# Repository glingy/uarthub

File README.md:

# UART Hub

This is a 6-port "null modem cable". There are six 4-signal UART channels with flow control. Each channel is connected to all six RP2040's at each USB port to allow full software configuration of which USB ports communicate on which channels. 

For example with the following configuration:
```
Channel 0: Port 0, Port 1
Channel 1: Port 0, Port 2
Channel 2: Port 1, Port 3
Channel 3: Port 1, Port 2
Channel 4: Port 0, Port 1
Channel 5: Port 0, External
```

A computer connected to USB 0 will see four USB CDC-ACM serial ports (COM ports on Windows, TTY's on Linux). They will be connected to USB 1, USB 2, USB 1, and the external pins labeled `5` respectively. Port 1 will also have four serial ports (USB 0, USB 3, USB 2, USB 0). Note that in this case there are two independent serial connections between USB 0 and 1. USB 2 will have two serial ports, USB 3 will only see one port, and USB 4 & 5 will see no serial ports. 

USB 0 will also have an additional management serial port that allows runtime configuration of which ports are associated with each channel via a terminal-based UI.

This project is not intended to work for other protocols (I2C, SPI), but the hardware should be capable of supporting I2C or SPI devices on the external pins, the RP2040 uses the same pins for I2C/SPI as it does for UART.

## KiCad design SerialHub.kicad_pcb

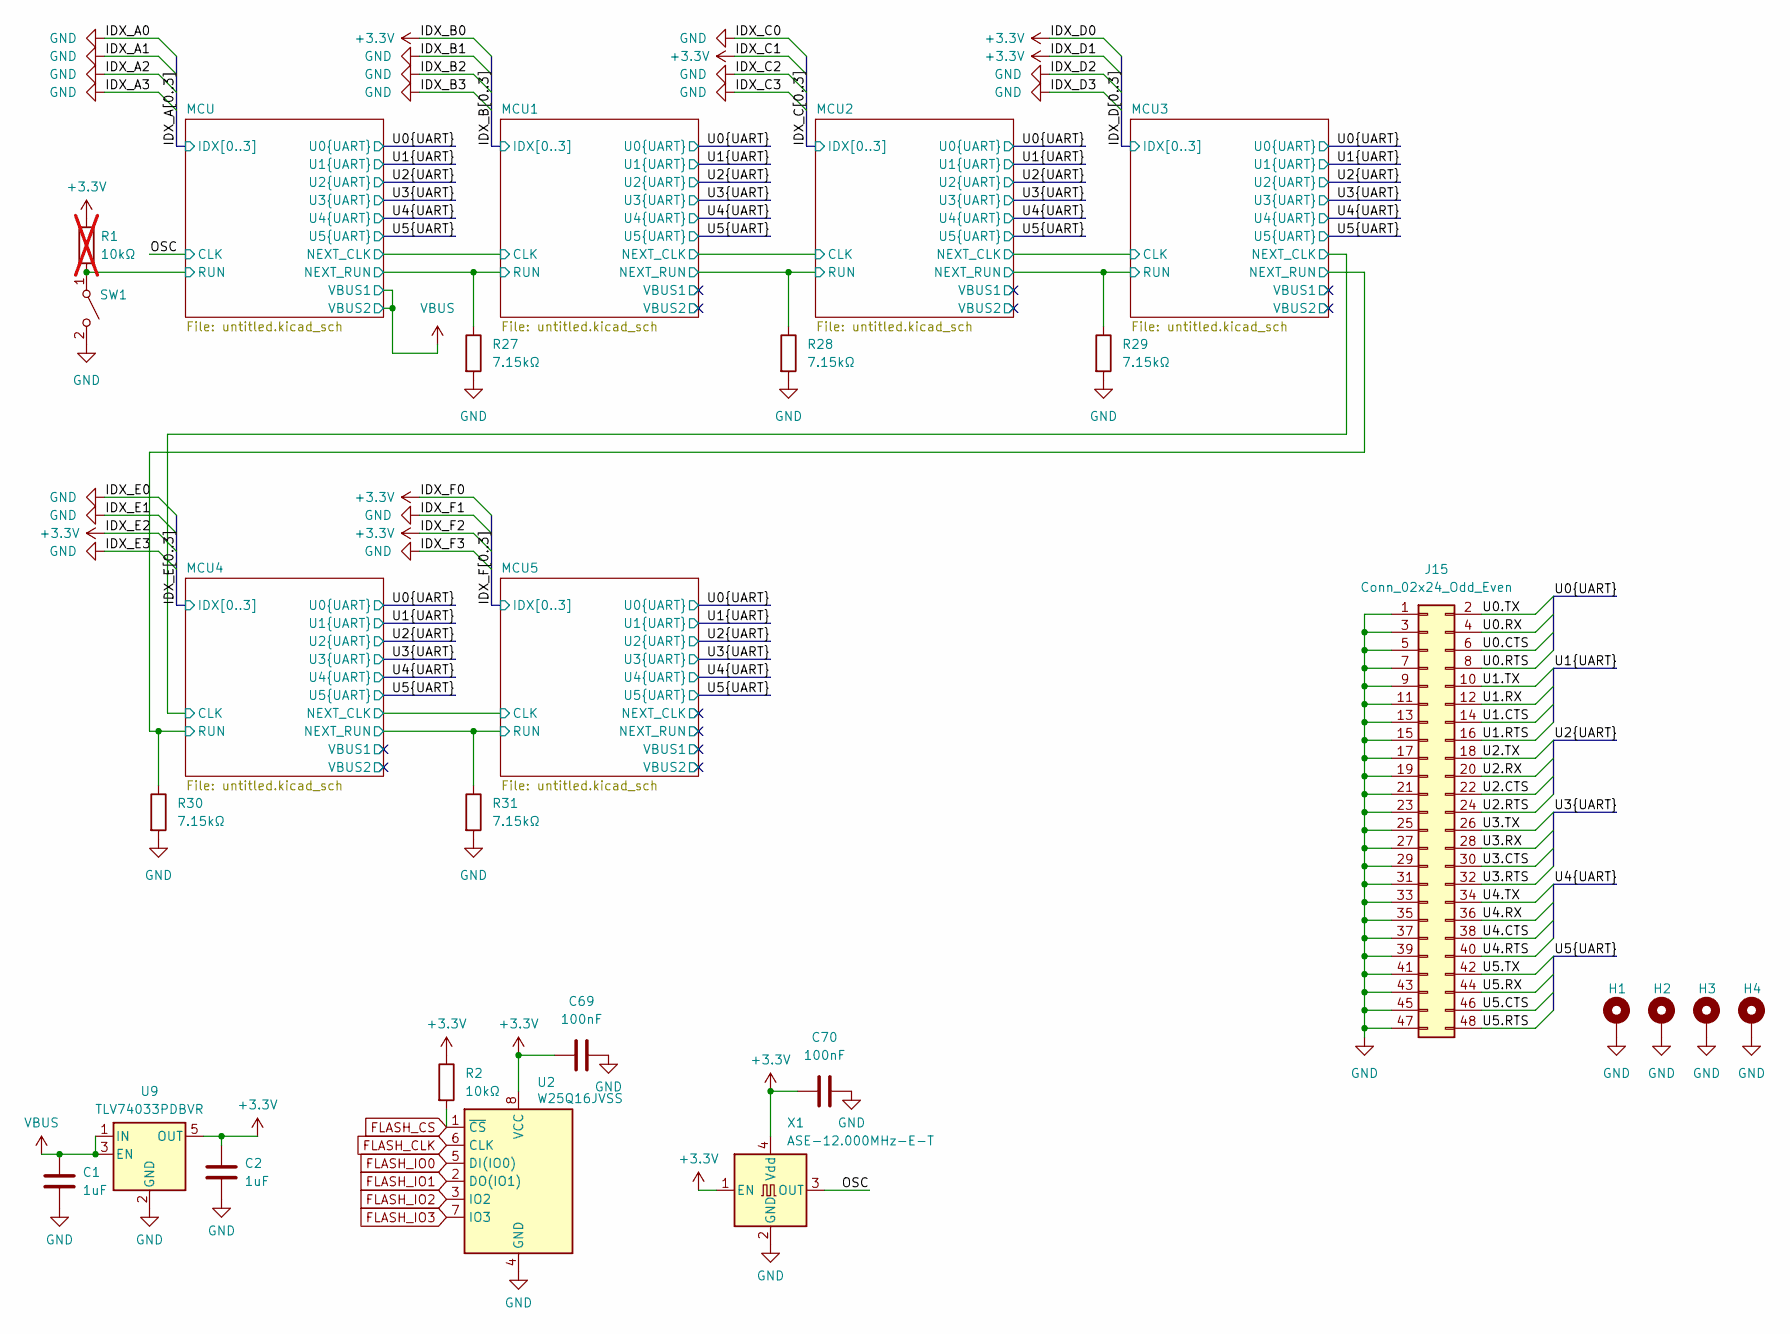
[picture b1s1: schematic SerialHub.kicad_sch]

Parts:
C1, C2: 1uF; C_0402_1005Metric; Digikey 399-C0402C105K9PACTUCT-ND
C69, C70: 100nF; C_0402_1005Metric; Digikey 399-C0402C105K9PACTUCT-ND
H1, H2, H3, H4: MountingHole_Pad; MountingHole_3.2mm_M3_Pad
J15: Conn_02x24_Odd_Even; PinHeader_2x24_P2.54mm_Vertical
R1: 10kΩ; R_0402_1005Metric; Digikey 311-10KJRCT-ND; not fitted
R2: 10kΩ; R_0402_1005Metric; Digikey 311-10KJRCT-ND
R27, R28, R29, R30, R31: 7.15kΩ; R_0402_1005Metric; Digikey YAG3235CT-ND
SW1: SW_SPST; SW_PUSH_6mm_H4.3mm; Digikey 2223-TS02-66-43-BK-160-LCR-D-ND
U2: W25Q16JVSS; SOIC-8_5.3x5.3mm_P1.27mm; Digikey 256-W25Q16JVSSIQTRCT-ND
U9: TLV74033PDBVR; SOT-23-5; Digikey 296-TLV74033PDBVRCT-ND
X1: ASE-12.000MHz-E-T; Oscillator_SMD_Abracon_ASE-4Pin_3.2x2.5mm; Digikey 535-ASE-12.000MHZ-E-TCT-ND

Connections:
+3.3V: C2.1, C69.1, C70.1, R1.2, R2.1, U2.8 (VCC), U9.5 (OUT), X1.1 (EN), X1.4 (Vdd); also elsewhere on the board
/MCU1/NEXT_RUN: R28.1; also elsewhere on the board
/MCU2/NEXT_RUN: R29.1; also elsewhere on the board
/MCU3/NEXT_RUN: R30.1; also elsewhere on the board
/MCU4/NEXT_RUN: R31.1; also elsewhere on the board
/MCU/NEXT_RUN: R27.1; also elsewhere on the board
/MCU/RUN: R1.1, SW1.1 (A); also elsewhere on the board
/OSC: X1.3 (OUT); also elsewhere on the board
/U0.CTS: J15.6; also elsewhere on the board
/U0.RTS: J15.8; also elsewhere on the board
/U0.RX: J15.4; also elsewhere on the board
/U0.TX: J15.2; also elsewhere on the board
/U1.CTS: J15.14; also elsewhere on the board
/U1.RTS: J15.16; also elsewhere on the board
/U1.RX: J15.12; also elsewhere on the board
/U1.TX: J15.10; also elsewhere on the board
/U2.CTS: J15.22; also elsewhere on the board
/U2.RTS: J15.24; also elsewhere on the board
/U2.RX: J15.20; also elsewhere on the board
/U2.TX: J15.18; also elsewhere on the board
/U3.CTS: J15.30; also elsewhere on the board
/U3.RTS: J15.32; also elsewhere on the board
/U3.RX: J15.28; also elsewhere on the board
/U3.TX: J15.26; also elsewhere on the board
/U4.CTS: J15.38; also elsewhere on the board
/U4.RTS: J15.40; also elsewhere on the board
/U4.RX: J15.36; also elsewhere on the board
/U4.TX: J15.34; also elsewhere on the board
/U5.CTS: J15.46; also elsewhere on the board
/U5.RTS: J15.48; also elsewhere on the board
/U5.RX: J15.44; also elsewhere on the board
/U5.TX: J15.42; also elsewhere on the board
FLASH_CLK: U2.6 (CLK); also elsewhere on the board
FLASH_CS: R2.2, U2.1 (~CS); also elsewhere on the board
FLASH_IO0: U2.5 (DI(IO0)); also elsewhere on the board
FLASH_IO1: U2.2 (DO(IO1)); also elsewhere on the board
FLASH_IO2: U2.3 (IO2); also elsewhere on the board
FLASH_IO3: U2.7 (IO3); also elsewhere on the board
VBUS: C1.1, U9.1 (IN), U9.3 (EN); also elsewhere on the board

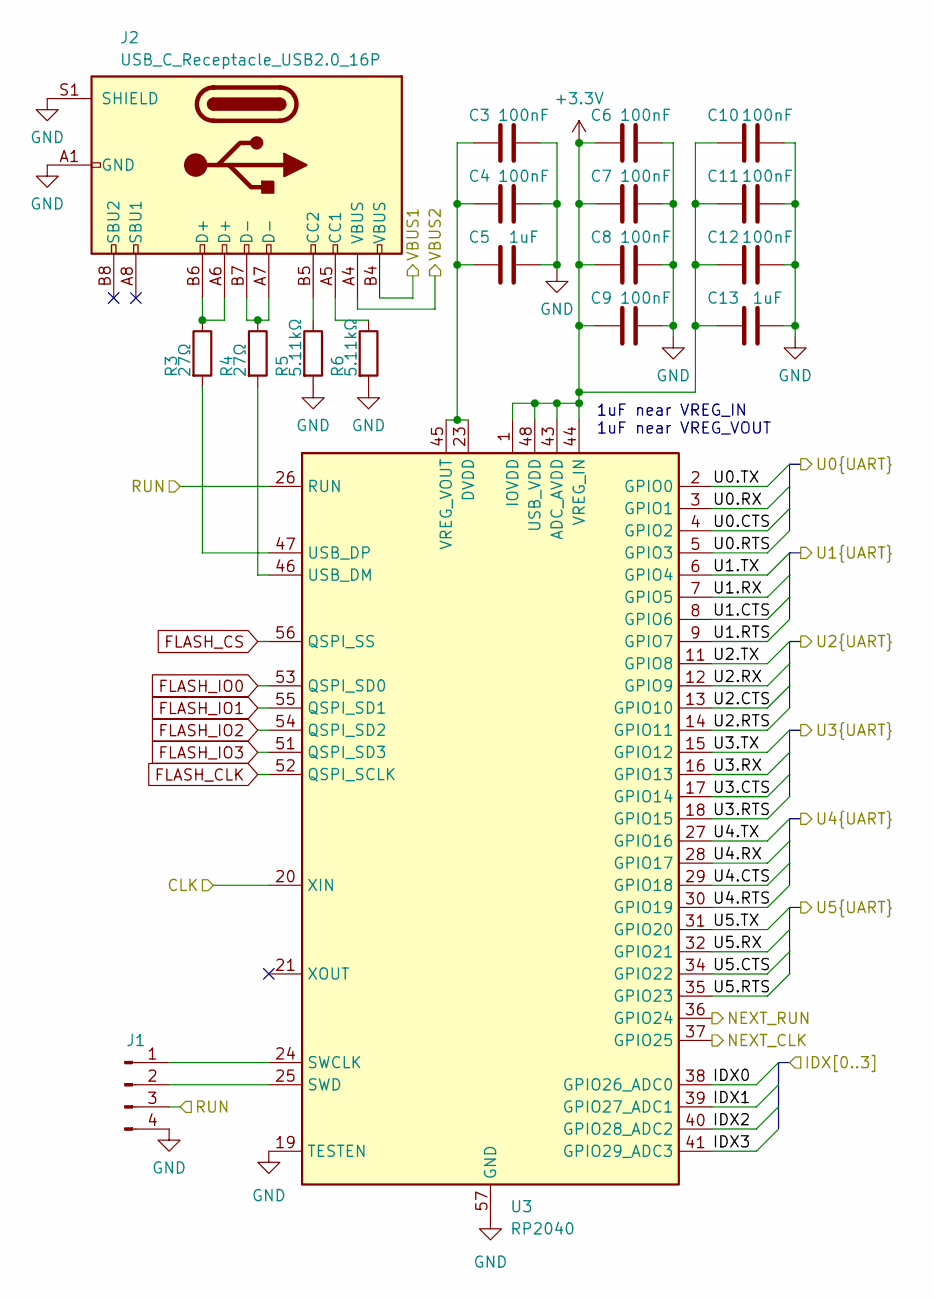
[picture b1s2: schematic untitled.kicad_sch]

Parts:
C3, C4, C6, C7, C8, C9, C10, C11, C12: 100nF; C_0402_1005Metric; Digikey 1276-1043-1-ND
C5, C13: 1uF; C_0402_1005Metric; Digikey 399-C0402C105K9PACTUCT-ND
J1: Conn_01x04_Pin; SaleaeTestpoint4
J2: USB_C_Receptacle_USB2.0_16P; SAMESKY_UJ20-C-H-G-SMT-1-P16-TR; Digikey 2223-UJ20-C-H-G-SMT-1-P16-TRCT-ND
R3, R4: 27Ω; R_0402_1005Metric; Digikey YAG5278CT-ND
R5, R6: 5.11kΩ; R_0402_1005Metric; Digikey RMCF0402FT5K11CT-ND
U3: RP2040; QFN-56-1EP_7x7mm_P0.4mm_EP3.2x3.2mm; Digikey 2648-SC0914(13)CT-ND

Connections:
+3.3V: C6.1, C7.1, C8.1, C9.1, C10.1, C11.1, C12.1, C13.1, U3.1 (IOVDD), U3.10 (IOVDD), U3.22 (IOVDD), U3.33 (IOVDD), U3.42 (IOVDD), U3.43 (ADC_AVDD), U3.44 (VREG_IN), U3.48 (USB_VDD), U3.49 (IOVDD); also elsewhere on the board
/MCU/NEXT_CLK: U3.37 (GPIO25); also elsewhere on the board
/MCU/NEXT_RUN: U3.36 (GPIO24); also elsewhere on the board
/MCU/RUN: J1.3, U3.26 (RUN); also elsewhere on the board
/OSC: U3.20 (XIN); also elsewhere on the board
/U0.CTS: U3.4 (GPIO2); also elsewhere on the board
/U0.RTS: U3.5 (GPIO3); also elsewhere on the board
/U0.RX: U3.3 (GPIO1); also elsewhere on the board
/U0.TX: U3.2 (GPIO0); also elsewhere on the board
/U1.CTS: U3.8 (GPIO6); also elsewhere on the board
/U1.RTS: U3.9 (GPIO7); also elsewhere on the board
/U1.RX: U3.7 (GPIO5); also elsewhere on the board
/U1.TX: U3.6 (GPIO4); also elsewhere on the board
/U2.CTS: U3.13 (GPIO10); also elsewhere on the board
/U2.RTS: U3.14 (GPIO11); also elsewhere on the board
/U2.RX: U3.12 (GPIO9); also elsewhere on the board
/U2.TX: U3.11 (GPIO8); also elsewhere on the board
/U3.CTS: U3.17 (GPIO14); also elsewhere on the board
/U3.RTS: U3.18 (GPIO15); also elsewhere on the board
/U3.RX: U3.16 (GPIO13); also elsewhere on the board
/U3.TX: U3.15 (GPIO12); also elsewhere on the board
/U4.CTS: U3.29 (GPIO18); also elsewhere on the board
/U4.RTS: U3.30 (GPIO19); also elsewhere on the board
/U4.RX: U3.28 (GPIO17); also elsewhere on the board
/U4.TX: U3.27 (GPIO16); also elsewhere on the board
/U5.CTS: U3.34 (GPIO22); also elsewhere on the board
/U5.RTS: U3.35 (GPIO23); also elsewhere on the board
/U5.RX: U3.32 (GPIO21); also elsewhere on the board
/U5.TX: U3.31 (GPIO20); also elsewhere on the board
FLASH_CLK: U3.52 (QSPI_SCLK); also elsewhere on the board
FLASH_CS: U3.56 (QSPI_SS); also elsewhere on the board
FLASH_IO0: U3.53 (QSPI_SD0); also elsewhere on the board
FLASH_IO1: U3.55 (QSPI_SD1); also elsewhere on the board
FLASH_IO2: U3.54 (QSPI_SD2); also elsewhere on the board
FLASH_IO3: U3.51 (QSPI_SD3); also elsewhere on the board
unnamed: J1.1, U3.24 (SWCLK)
unnamed: J1.2, U3.25 (SWD)
unnamed: J2.A5 (CC1), R6.1
unnamed: J2.B5 (CC2), R5.1
unnamed: J2.A6 (D+), J2.B6 (D+), R3.1
unnamed: J2.A7 (D-), J2.B7 (D-), R4.1
unnamed: R4.2, U3.46 (USB_DM)
unnamed: R3.2, U3.47 (USB_DP)
unnamed: C3.1, C4.1, C5.1, U3.23 (DVDD), U3.45 (VREG_VOUT), U3.50 (DVDD)
VBUS: J2.A4 (VBUS), J2.B4 (VBUS); also elsewhere on the board

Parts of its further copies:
C14, C15, C17, C18, C19, C20, C21, C22, C23, C25, C26, C28, C29, C30, C31, C32, C33, C34, C36, C37, C39, C40, C41, C42, C43, C44, C45, C47, C48, C50, C51, C52, C53, C54, C55, C56, C58, C59, C61, C62, C63, C64, C65, C66, C67: 100nF; C_0402_1005Metric; Digikey 1276-1043-1-ND
C16, C24, C27, C35, C38, C46, C49, C57, C60, C68: 1uF; C_0402_1005Metric; Digikey 399-C0402C105K9PACTUCT-ND
J3, J5, J7, J9, J11: Conn_01x04_Pin; SaleaeTestpoint4
J4, J6, J8, J10, J12: USB_C_Receptacle_USB2.0_16P; SAMESKY_UJ20-C-H-G-SMT-1-P16-TR; Digikey 2223-UJ20-C-H-G-SMT-1-P16-TRCT-ND
R7, R8, R11, R12, R15, R16, R19, R20, R23, R24: 27Ω; R_0402_1005Metric; Digikey YAG5278CT-ND
R9, R10, R13, R14, R17, R18, R21, R22, R25, R26: 5.11kΩ; R_0402_1005Metric; Digikey RMCF0402FT5K11CT-ND
U4, U5, U6, U7, U8: RP2040; QFN-56-1EP_7x7mm_P0.4mm_EP3.2x3.2mm; Digikey 2648-SC0914(13)CT-ND

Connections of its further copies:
+3.3V: C17.1, C18.1, C19.1, C20.1, C21.1, C22.1, C23.1, C24.1, C28.1, C29.1, C30.1, C31.1, C32.1, C33.1, C34.1, C35.1, C39.1, C40.1, C41.1, C42.1, C43.1, C44.1, C45.1, C46.1, C50.1, C51.1, C52.1, C53.1, C54.1, C55.1, C56.1, C57.1, C61.1, C62.1, C63.1, C64.1, C65.1, C66.1, C67.1, C68.1, U4.1 (IOVDD), U4.10 (IOVDD), U4.22 (IOVDD), U4.33 (IOVDD), U4.38 (GPIO26_ADC0), U4.42 (IOVDD), U4.43 (ADC_AVDD), U4.44 (VREG_IN), U4.48 (USB_VDD), U4.49 (IOVDD), U5.1 (IOVDD), U5.10 (IOVDD), U5.22 (IOVDD), U5.33 (IOVDD), U5.39 (GPIO27_ADC1), U5.42 (IOVDD), U5.43 (ADC_AVDD), U5.44 (VREG_IN), U5.48 (USB_VDD), U5.49 (IOVDD), U6.1 (IOVDD), U6.10 (IOVDD), U6.22 (IOVDD), U6.33 (IOVDD), U6.38 (GPIO26_ADC0), U6.39 (GPIO27_ADC1), U6.42 (IOVDD), U6.43 (ADC_AVDD), U6.44 (VREG_IN), U6.48 (USB_VDD), U6.49 (IOVDD), U7.1 (IOVDD), U7.10 (IOVDD), U7.22 (IOVDD), U7.33 (IOVDD), U7.40 (GPIO28_ADC2), U7.42 (IOVDD), U7.43 (ADC_AVDD), U7.44 (VREG_IN), U7.48 (USB_VDD), U7.49 (IOVDD), U8.1 (IOVDD), U8.10 (IOVDD), U8.22 (IOVDD), U8.33 (IOVDD), U8.38 (GPIO26_ADC0), U8.40 (GPIO28_ADC2), U8.42 (IOVDD), U8.43 (ADC_AVDD), U8.44 (VREG_IN), U8.48 (USB_VDD), U8.49 (IOVDD); also elsewhere on the board
/MCU1/NEXT_CLK: U4.37 (GPIO25), U5.20 (XIN)
/MCU1/NEXT_RUN: J5.3, U4.36 (GPIO24), U5.26 (RUN); also elsewhere on the board
/MCU1/VBUS1: J4.B4 (VBUS)
/MCU1/VBUS2: J4.A4 (VBUS)
/MCU2/NEXT_CLK: U5.37 (GPIO25), U6.20 (XIN)
/MCU2/NEXT_RUN: J7.3, U5.36 (GPIO24), U6.26 (RUN); also elsewhere on the board
/MCU2/VBUS1: J6.B4 (VBUS)
/MCU2/VBUS2: J6.A4 (VBUS)
/MCU3/NEXT_CLK: U6.37 (GPIO25), U7.20 (XIN)
/MCU3/NEXT_RUN: J9.3, U6.36 (GPIO24), U7.26 (RUN); also elsewhere on the board
/MCU3/VBUS1: J8.B4 (VBUS)
/MCU3/VBUS2: J8.A4 (VBUS)
/MCU4/NEXT_CLK: U7.37 (GPIO25), U8.20 (XIN)
/MCU4/NEXT_RUN: J11.3, U7.36 (GPIO24), U8.26 (RUN); also elsewhere on the board
/MCU4/VBUS1: J10.B4 (VBUS)
/MCU4/VBUS2: J10.A4 (VBUS)
/MCU5/NEXT_CLK: U8.37 (GPIO25)
/MCU5/NEXT_RUN: U8.36 (GPIO24)
/MCU5/VBUS1: J12.B4 (VBUS)
/MCU5/VBUS2: J12.A4 (VBUS)
/MCU/NEXT_CLK: U4.20 (XIN); also elsewhere on the board
/MCU/NEXT_RUN: J3.3, U4.26 (RUN); also elsewhere on the board
/U0.CTS: U4.4 (GPIO2), U5.4 (GPIO2), U6.4 (GPIO2), U7.4 (GPIO2), U8.4 (GPIO2); also elsewhere on the board
/U0.RTS: U4.5 (GPIO3), U5.5 (GPIO3), U6.5 (GPIO3), U7.5 (GPIO3), U8.5 (GPIO3); also elsewhere on the board
/U0.RX: U4.3 (GPIO1), U5.3 (GPIO1), U6.3 (GPIO1), U7.3 (GPIO1), U8.3 (GPIO1); also elsewhere on the board
/U0.TX: U4.2 (GPIO0), U5.2 (GPIO0), U6.2 (GPIO0), U7.2 (GPIO0), U8.2 (GPIO0); also elsewhere on the board
/U1.CTS: U4.8 (GPIO6), U5.8 (GPIO6), U6.8 (GPIO6), U7.8 (GPIO6), U8.8 (GPIO6); also elsewhere on the board
/U1.RTS: U4.9 (GPIO7), U5.9 (GPIO7), U6.9 (GPIO7), U7.9 (GPIO7), U8.9 (GPIO7); also elsewhere on the board
/U1.RX: U4.7 (GPIO5), U5.7 (GPIO5), U6.7 (GPIO5), U7.7 (GPIO5), U8.7 (GPIO5); also elsewhere on the board
/U1.TX: U4.6 (GPIO4), U5.6 (GPIO4), U6.6 (GPIO4), U7.6 (GPIO4), U8.6 (GPIO4); also elsewhere on the board
/U2.CTS: U4.13 (GPIO10), U5.13 (GPIO10), U6.13 (GPIO10), U7.13 (GPIO10), U8.13 (GPIO10); also elsewhere on the board
/U2.RTS: U4.14 (GPIO11), U5.14 (GPIO11), U6.14 (GPIO11), U7.14 (GPIO11), U8.14 (GPIO11); also elsewhere on the board
/U2.RX: U4.12 (GPIO9), U5.12 (GPIO9), U6.12 (GPIO9), U7.12 (GPIO9), U8.12 (GPIO9); also elsewhere on the board
/U2.TX: U4.11 (GPIO8), U5.11 (GPIO8), U6.11 (GPIO8), U7.11 (GPIO8), U8.11 (GPIO8); also elsewhere on the board
/U3.CTS: U4.17 (GPIO14), U5.17 (GPIO14), U6.17 (GPIO14), U7.17 (GPIO14), U8.17 (GPIO14); also elsewhere on the board
/U3.RTS: U4.18 (GPIO15), U5.18 (GPIO15), U6.18 (GPIO15), U7.18 (GPIO15), U8.18 (GPIO15); also elsewhere on the board
/U3.RX: U4.16 (GPIO13), U5.16 (GPIO13), U6.16 (GPIO13), U7.16 (GPIO13), U8.16 (GPIO13); also elsewhere on the board
/U3.TX: U4.15 (GPIO12), U5.15 (GPIO12), U6.15 (GPIO12), U7.15 (GPIO12), U8.15 (GPIO12); also elsewhere on the board
/U4.CTS: U4.29 (GPIO18), U5.29 (GPIO18), U6.29 (GPIO18), U7.29 (GPIO18), U8.29 (GPIO18); also elsewhere on the board
/U4.RTS: U4.30 (GPIO19), U5.30 (GPIO19), U6.30 (GPIO19), U7.30 (GPIO19), U8.30 (GPIO19); also elsewhere on the board
/U4.RX: U4.28 (GPIO17), U5.28 (GPIO17), U6.28 (GPIO17), U7.28 (GPIO17), U8.28 (GPIO17); also elsewhere on the board
/U4.TX: U4.27 (GPIO16), U5.27 (GPIO16), U6.27 (GPIO16), U7.27 (GPIO16), U8.27 (GPIO16); also elsewhere on the board
/U5.CTS: U4.34 (GPIO22), U5.34 (GPIO22), U6.34 (GPIO22), U7.34 (GPIO22), U8.34 (GPIO22); also elsewhere on the board
/U5.RTS: U4.35 (GPIO23), U5.35 (GPIO23), U6.35 (GPIO23), U7.35 (GPIO23), U8.35 (GPIO23); also elsewhere on the board
/U5.RX: U4.32 (GPIO21), U5.32 (GPIO21), U6.32 (GPIO21), U7.32 (GPIO21), U8.32 (GPIO21); also elsewhere on the board
/U5.TX: U4.31 (GPIO20), U5.31 (GPIO20), U6.31 (GPIO20), U7.31 (GPIO20), U8.31 (GPIO20); also elsewhere on the board
FLASH_CLK: U4.52 (QSPI_SCLK), U5.52 (QSPI_SCLK), U6.52 (QSPI_SCLK), U7.52 (QSPI_SCLK), U8.52 (QSPI_SCLK); also elsewhere on the board
FLASH_CS: U4.56 (QSPI_SS), U5.56 (QSPI_SS), U6.56 (QSPI_SS), U7.56 (QSPI_SS), U8.56 (QSPI_SS); also elsewhere on the board
FLASH_IO0: U4.53 (QSPI_SD0), U5.53 (QSPI_SD0), U6.53 (QSPI_SD0), U7.53 (QSPI_SD0), U8.53 (QSPI_SD0); also elsewhere on the board
FLASH_IO1: U4.55 (QSPI_SD1), U5.55 (QSPI_SD1), U6.55 (QSPI_SD1), U7.55 (QSPI_SD1), U8.55 (QSPI_SD1); also elsewhere on the board
FLASH_IO2: U4.54 (QSPI_SD2), U5.54 (QSPI_SD2), U6.54 (QSPI_SD2), U7.54 (QSPI_SD2), U8.54 (QSPI_SD2); also elsewhere on the board
FLASH_IO3: U4.51 (QSPI_SD3), U5.51 (QSPI_SD3), U6.51 (QSPI_SD3), U7.51 (QSPI_SD3), U8.51 (QSPI_SD3); also elsewhere on the board
unnamed: J3.1, U4.24 (SWCLK)
unnamed: J3.2, U4.25 (SWD)
unnamed: J4.A5 (CC1), R10.1
unnamed: J4.B5 (CC2), R9.1
unnamed: J4.A6 (D+), J4.B6 (D+), R7.1
unnamed: J4.A7 (D-), J4.B7 (D-), R8.1
unnamed: J5.1, U5.24 (SWCLK)
unnamed: J5.2, U5.25 (SWD)
unnamed: J6.A5 (CC1), R14.1
unnamed: J6.B5 (CC2), R13.1
unnamed: J6.A6 (D+), J6.B6 (D+), R11.1
unnamed: J6.A7 (D-), J6.B7 (D-), R12.1
unnamed: J7.1, U6.24 (SWCLK)
unnamed: J7.2, U6.25 (SWD)
unnamed: J8.A5 (CC1), R18.1
unnamed: J8.B5 (CC2), R17.1
unnamed: J8.A6 (D+), J8.B6 (D+), R15.1
unnamed: J8.A7 (D-), J8.B7 (D-), R16.1
unnamed: J9.1, U7.24 (SWCLK)
unnamed: J9.2, U7.25 (SWD)
unnamed: J10.A5 (CC1), R22.1
unnamed: J10.B5 (CC2), R21.1
unnamed: J10.A6 (D+), J10.B6 (D+), R19.1
unnamed: J10.A7 (D-), J10.B7 (D-), R20.1
unnamed: J11.1, U8.24 (SWCLK)
unnamed: J11.2, U8.25 (SWD)
unnamed: J12.A5 (CC1), R26.1
unnamed: J12.B5 (CC2), R25.1
unnamed: J12.A6 (D+), J12.B6 (D+), R23.1
unnamed: J12.A7 (D-), J12.B7 (D-), R24.1
unnamed: R8.2, U4.46 (USB_DM)
unnamed: R7.2, U4.47 (USB_DP)
unnamed: C14.1, C15.1, C16.1, U4.23 (DVDD), U4.45 (VREG_VOUT), U4.50 (DVDD)
unnamed: R12.2, U5.46 (USB_DM)
unnamed: R11.2, U5.47 (USB_DP)
unnamed: C25.1, C26.1, C27.1, U5.23 (DVDD), U5.45 (VREG_VOUT), U5.50 (DVDD)
unnamed: R16.2, U6.46 (USB_DM)
unnamed: R15.2, U6.47 (USB_DP)
unnamed: C36.1, C37.1, C38.1, U6.23 (DVDD), U6.45 (VREG_VOUT), U6.50 (DVDD)
unnamed: R20.2, U7.46 (USB_DM)
unnamed: R19.2, U7.47 (USB_DP)
unnamed: C47.1, C48.1, C49.1, U7.23 (DVDD), U7.45 (VREG_VOUT), U7.50 (DVDD)
unnamed: R24.2, U8.46 (USB_DM)
unnamed: R23.2, U8.47 (USB_DP)
unnamed: C58.1, C59.1, C60.1, U8.23 (DVDD), U8.45 (VREG_VOUT), U8.50 (DVDD)

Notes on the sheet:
1uF near VREG_IN 1uF near VREG_VOUT

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
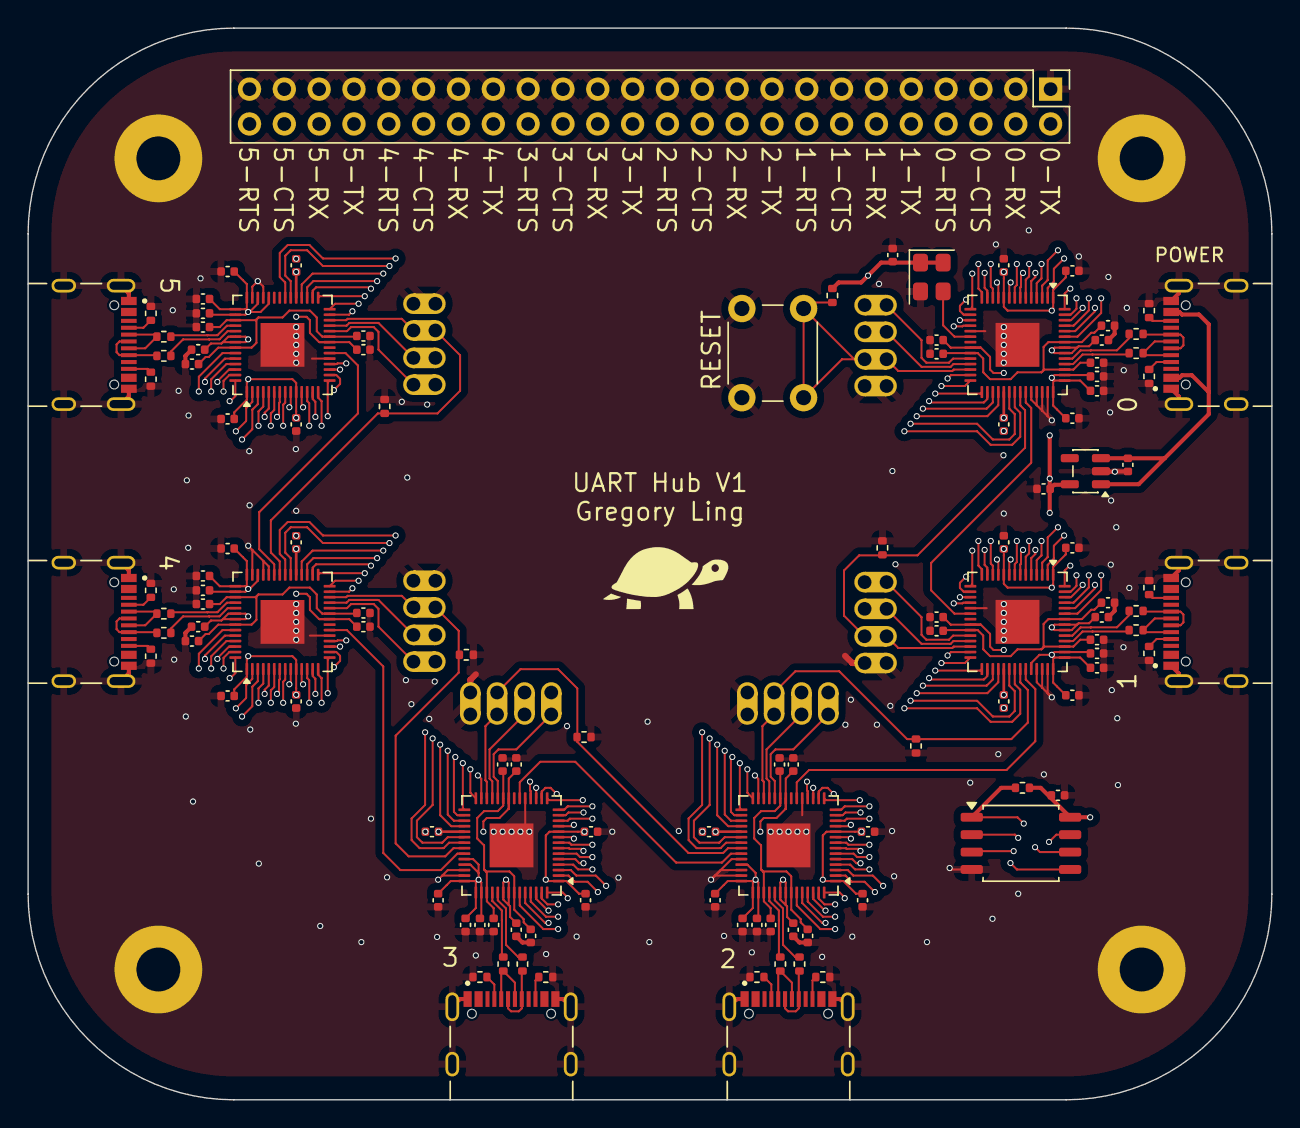
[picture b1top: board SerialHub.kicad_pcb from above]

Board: 4 copper layers, 90.7 x 78.2 mm, 128 parts (0 on the bottom side), 99 nets.

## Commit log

2025-10-25 Add README
2025-10-25 Added Schematic PDF
2025-10-29 Order
